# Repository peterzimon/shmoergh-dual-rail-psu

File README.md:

# +/-12V Dual rail power supply

Based on (Banana Schplit)[https://github.com/pms67/BananaSchplit] by Philip Salmony

# History

### v0.1-not-working

- well, it doesn't work. The layout is shit

### v1

- working version, using the exact same layout as Phil with Banana Schplit

#

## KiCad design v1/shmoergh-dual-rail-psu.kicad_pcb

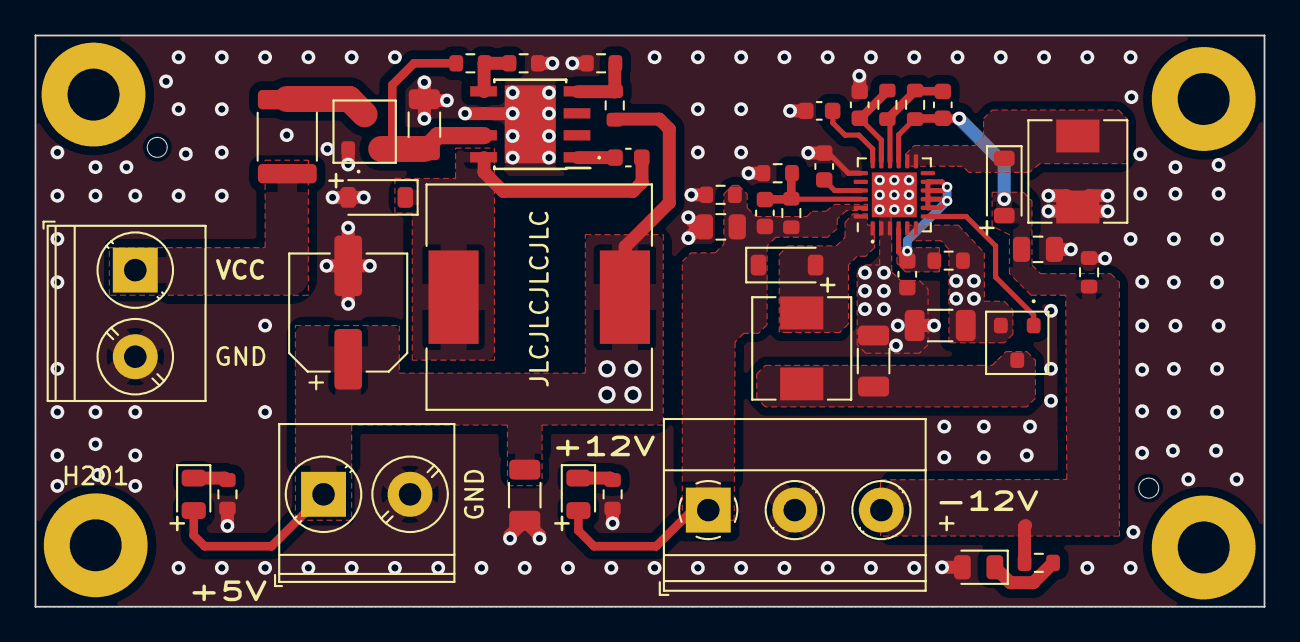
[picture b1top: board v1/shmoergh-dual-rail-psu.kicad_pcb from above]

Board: 4 copper layers, 71.0 x 33.0 mm, 49 parts (0 on the bottom side), 24 nets.

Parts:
C101, C102, C103, C107: 10u; C_1206_3216Metric
C104: 100n; C_0603_1608Metric
C105, C106: 10n; C_0603_1608Metric
C108: 6p8; C_0603_1608Metric
C109: 8p2; C_0603_1608Metric
C110: 220u; CP_Elec_6.3x7.7
C111: 220n; C_0603_1608Metric
C112, C113: 22u; C_0805_2012Metric
C114: 4n7; C_0603_1608Metric
D101, D102, D103: B5819W; D_SOD-123
D104: RED; LED_0805_2012Metric
D105: GREEN; LED_0805_2012Metric
D106: YELLOW; LED_0805_2012Metric
F101: 500mA; Fuse_1812_4532Metric
H201, H202, H203, H204: MountingHole; MountingHole_3mm_Pad
J101, J103: Screw_Terminal_01x02; TerminalBlock_Phoenix_PT-1,5-2-5.0-H_1x02_P5.00mm_Horizontal
J102: Screw_Terminal_01x03; TerminalBlock_Phoenix_MKDS-1,5-3_1x03_P5.00mm_Horizontal
L101, L103: 10u; L_Sunlord_MWSA0518S
L102: 47u; L_Sunlord_SWRB1204S
Q101, Q102: AO3401A; SOT-23
R101: 100; R_0603_1608Metric
R102, R103, R106: 100k; R_0603_1608Metric
R104, R107: 1M; R_0603_1608Metric
R105: 110k; R_0603_1608Metric
R108: 10k; R_0603_1608Metric
R109: 3k3; R_0603_1608Metric
R110, R111: 12k; R_0603_1608Metric
R112: 1k5; R_0603_1608Metric
R113: 4k3; R_0603_1608Metric
R114: 5k1; R_0603_1608Metric
U101: TPS65131RGER; QFN-24-1EP_4x4mm_P0.5mm_EP2.6x2.6mm
U102: TPS5430DDA; TI_SO-PowerPAD-8_ThermalVias

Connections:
+5V: C101.1, C107.1, C110.1, D104.2 (A), J103.1, L102.2, Q102.2 (S), R101.2, R108.2, U101.5 (INN_1), U101.6 (INN_2)
+12V: C108.1, C113.1, D101.1 (K), D105.2 (A), J102.1, R104.2, R111.2, U101.23 (VPOS)
-12V: C109.2, C112.1, D103.2 (A), J102.3, R107.1, R110.2, R114.1, U101.15 (VNEG)
GND: C101.2, C102.2, C103.2, C104.2, C106.2, C107.2, C110.2, C111.2, C112.2, C113.2, C114.2, D102.2 (A), D106.2 (A), J101.2, J102.2, J103.2, L103.2, Q101.1 (G), R103.1, R105.1, R109.1, R110.1, R111.1, R112.1, R113.1, U101.2 (PGND_1), U101.3 (PGND_2), U101.19 (AGND), U101.25 (POWERPAD), U102.6 (GND), U102.9 (GNDPAD)
unnamed: D101.2 (A), L101.2, U101.1 (INP_1), U101.24 (INP_2)
unnamed: C105.2, D102.1 (K), L102.1, U102.8 (PH)
unnamed: D103.1 (K), L103.1, U101.13 (OUTN_1), U101.14 (OUTN_2)
unnamed: D104.1 (K), R112.2
unnamed: D105.1 (K), R113.2
unnamed: D106.1 (K), R114.2
unnamed: F101.1, Q101.3 (D)
unnamed: C102.1, Q101.2 (S), R102.2, U102.7 (VIN)
unnamed: C103.1, L101.1, Q102.3 (D)
unnamed: Q102.1 (G), U101.7 (BSW)
unnamed: C114.1, U101.18 (CN)
unnamed: C106.1, U101.21 (CP)
unnamed: C104.1, R101.1, U101.4 (VIN), U101.8 (ENP), U101.9 (PSP), U101.10 (ENN), U101.11 (PSN)
unnamed: C109.1, R106.1, R107.2, U101.16 (FBN)
unnamed: C108.2, R104.1, R105.2, U101.22 (FBP)
unnamed: C111.1, R106.2, U101.17 (VREF)
unnamed: C105.1, U102.1 (BOOT)
unnamed: R102.1, R103.2, U102.5 (EN)
PSU_FB: R108.1, R109.2, U102.4 (VSENSE)
VCC: F101.2, J101.1

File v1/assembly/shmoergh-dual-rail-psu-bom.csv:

Comment,Designator,Footprint,LCSC
"10u","C101,C102,C103,C107","Capacitor_SMD:C_1206_3216Metric","C13585"
"100n","C104","Capacitor_SMD:C_0603_1608Metric","C14663"
"10n","C105,C106","Capacitor_SMD:C_0603_1608Metric","C57112"
"6p8","C108","Capacitor_SMD:C_0603_1608Metric","C1679"
"8p2","C109","Capacitor_SMD:C_0603_1608Metric","C1685"
"220u","C110","Capacitor_SMD:CP_Elec_6.3x7.7","C127327"
"220n","C111","Capacitor_SMD:C_0603_1608Metric","C21120"
"22u","C112,C113","Capacitor_SMD:C_0805_2012Metric","C45783"
"4n7","C114","Capacitor_SMD:C_0603_1608Metric","C53987"
"B5819W","D101,D102,D103","Diode_SMD:D_SOD-123","C8598"
"RED","D104","LED_SMD:LED_0805_2012Metric","C84256"
"GREEN","D105","LED_SMD:LED_0805_2012Metric","C2297"
"YELLOW","D106","LED_SMD:LED_0805_2012Metric","C2296"
"500mA","F101","Fuse:Fuse_1812_4532Metric","C151168"
"10u","L101,L103","Inductor_SMD:L_Sunlord_MWSA0518S","C181721"
"47u","L102","Inductor_SMD:L_Sunlord_SWRB1204S","C169398"
"AO3401A","Q101,Q102","PCM_Package_TO_SOT_SMD_AKL:SOT-23","C15127"
"100","R101","Resistor_SMD:R_0603_1608Metric","C22775"
"100k","R102,R103,R106","Resistor_SMD:R_0603_1608Metric","C25803"
"1M","R104,R107","Resistor_SMD:R_0603_1608Metric","C22935"
"110k","R105","Resistor_SMD:R_0603_1608Metric","C25805"
"10k","R108","Resistor_SMD:R_0603_1608Metric","C25804"
"3k3","R109","Resistor_SMD:R_0603_1608Metric","C22978"
"12k","R110,R111","Resistor_SMD:R_0603_1608Metric","C22790"
"1k5","R112","Resistor_SMD:R_0603_1608Metric","C22843"
"4k3","R113","Resistor_SMD:R_0603_1608Metric","C23159"
"5k1","R114","Resistor_SMD:R_0603_1608Metric","C23186"
"TPS65131RGER","U101","Package_DFN_QFN:QFN-24-1EP_4x4mm_P0.5mm_EP2.6x2.6mm","C87663"
"TPS5430DDA","U102","Package_SO:TI_SO-PowerPAD-8_ThermalVias","C9864"

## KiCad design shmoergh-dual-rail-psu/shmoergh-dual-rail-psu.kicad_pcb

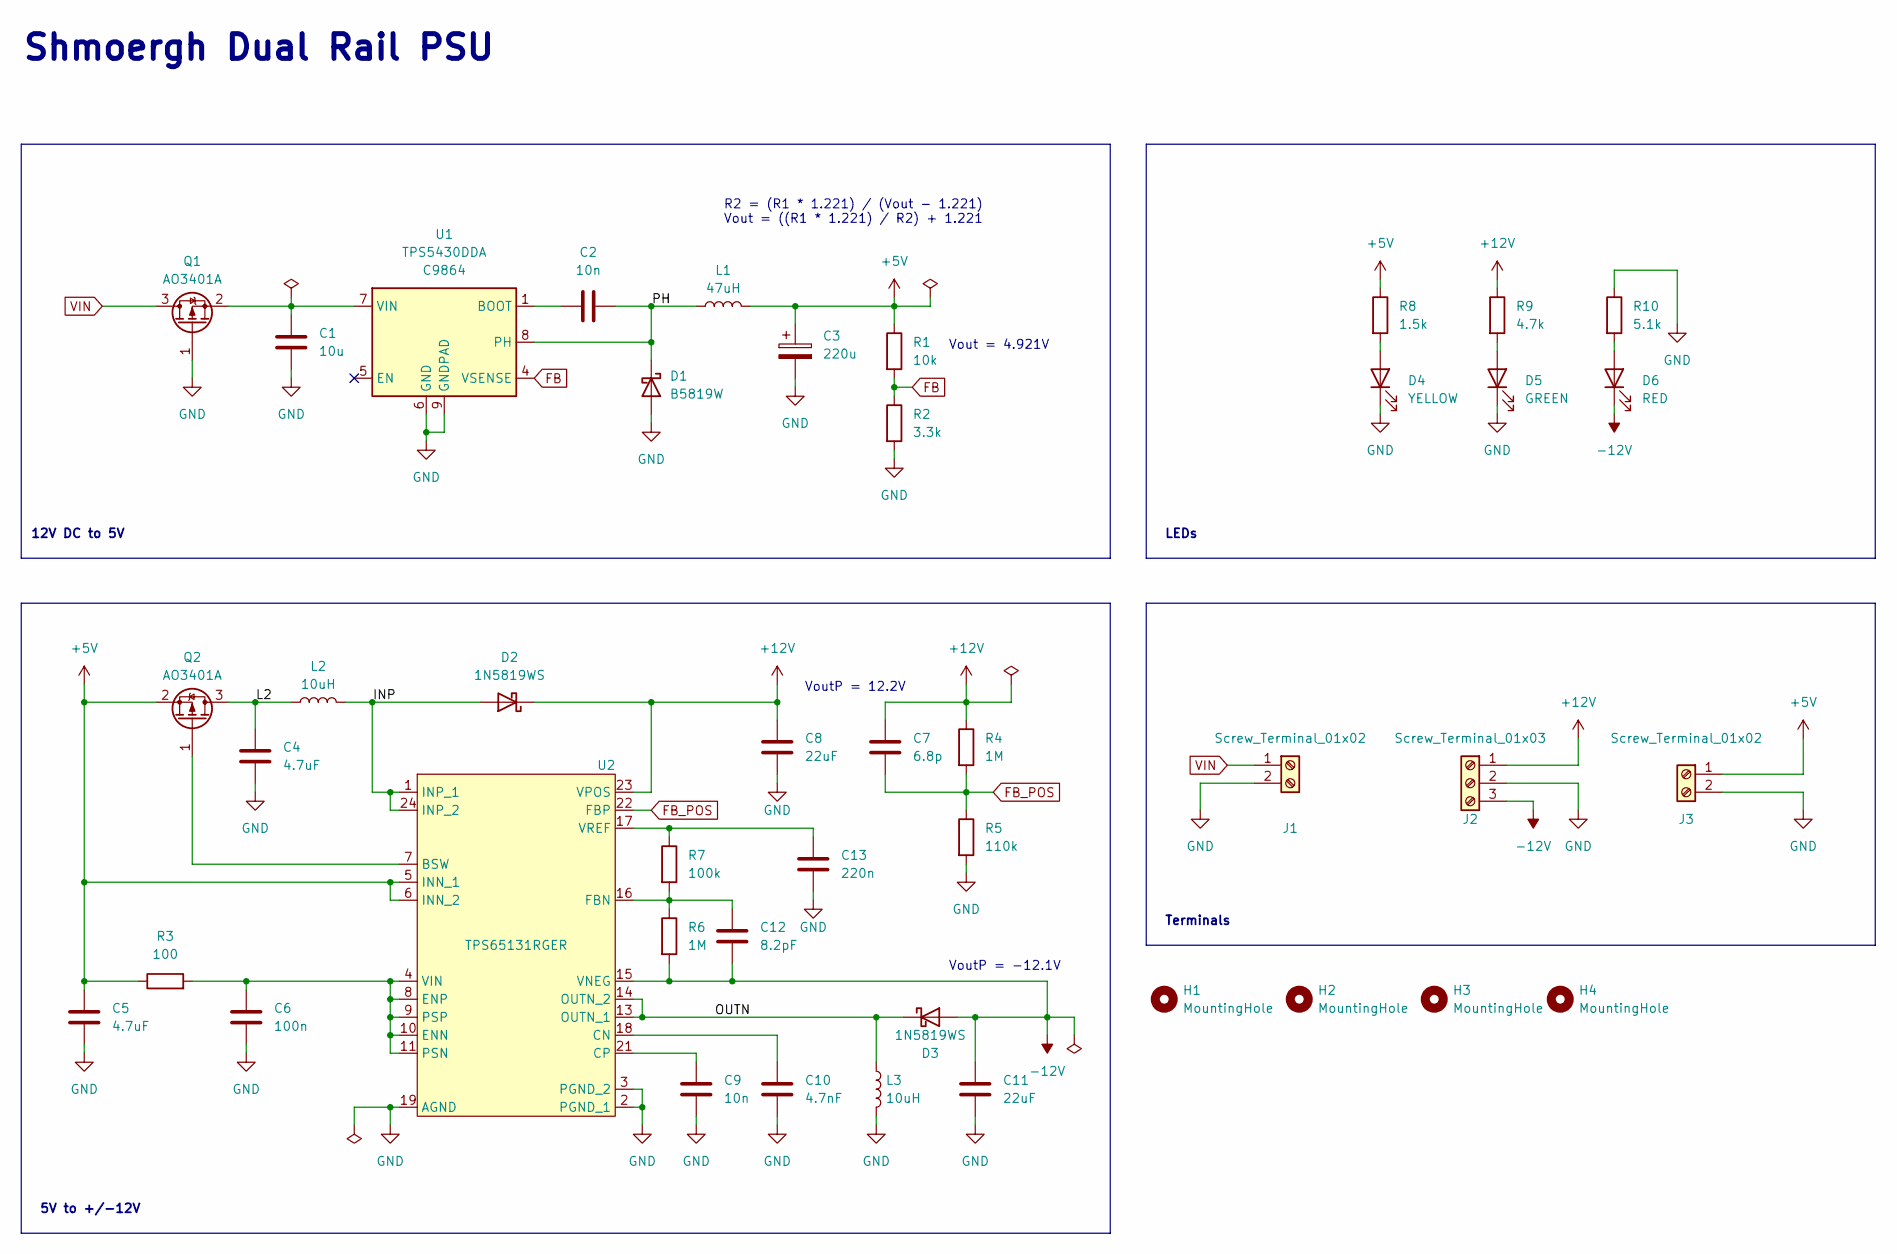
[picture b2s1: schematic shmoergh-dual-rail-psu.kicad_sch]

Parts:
C1: 10u; C_1206_3216Metric; LCSC C13585
C2: 10n; C_0402_1005Metric; LCSC C15195
C3: 220u; C_Elec_6.3x7.7; LCSC C127327
C4, C5: 4.7uF; C_0603_1608Metric; LCSC C19666
C6: 100n; C_0402_1005Metric; LCSC C307331
C7: 6.8p; R_0603_1608Metric; LCSC C1679
C8, C11: 22uF; C_0805_2012Metric; LCSC C45783
C9: 10n; C_0603_1608Metric; LCSC C57112
C10: 4.7nF; C_0603_1608Metric; LCSC C53987
C12: 8.2pF; C_0603_1608Metric; LCSC C1685
C13: 220n; C_0603_1608Metric; LCSC C21120
D1: B5819W; D_SOD-123; LCSC C8598
D2, D3: 1N5819WS; D_SOD-123; LCSC C191023
D4: YELLOW; LED_0603_1608Metric; LCSC C72038
D5: GREEN; LED_0603_1608Metric; LCSC C72043
D6: RED; LED_0603_1608Metric; LCSC C2286
H1, H2, H3, H4: MountingHole; MountingHole_3mm_Pad_Via
J1, J3: Screw_Terminal_01x02; TerminalBlock_Phoenix_MKDS-1,5-2_1x02_P5.00mm_Horizontal
J2: Screw_Terminal_01x03; TerminalBlock_Phoenix_MKDS-1,5-3_1x03_P5.00mm_Horizontal
L1: 47uH; L_Sunlord_SWRB1204S; LCSC C169398
L2, L3: 10uH; L_Sunlord_MWSA0518S; LCSC C177248
Q1, Q2: AO3401A; SOT-23; LCSC C15127
R1: 10k; R_0603_1608Metric; LCSC C25804
R2: 3.3k; R_0603_1608Metric; LCSC C22978
R3: 100; R_0603_1608Metric; LCSC C22775
R4, R6: 1M; R_0603_1608Metric; LCSC C22935
R5: 110k; R_0603_1608Metric; LCSC C25805
R7: 100k; R_0603_1608Metric; LCSC C25803
R8: 1.5k; R_0402_1005Metric; LCSC C25867
R9: 4.7k; R_0402_1005Metric; LCSC C25900
R10: 5.1k; R_0402_1005Metric; LCSC C25905
U1: TPS5430DDA; TI_SO-PowerPAD-8_ThermalVias; LCSC C9864
U2: TPS65131RGER; QFN-24-1EP_4x4mm_P0.5mm_EP2.6x2.6mm; LCSC TPS65131RGER

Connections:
+5V: C3.1, C5.1, J3.1, L1.2, Q2.2 (S), R1.1, R3.1, R8.1, U2.5 (INN_1), U2.6 (INN_2)
+12V: C7.1, C8.1, D2.1 (K), J2.1, R4.1, R9.1, U2.23 (VPOS)
-12V: C11.1, C12.2, D3.2 (A), D6.1 (K), J2.3, R6.2, U2.15 (VNEG)
/INP: D2.2 (A), L2.2, U2.1 (INP_1), U2.24 (INP_2)
/L2: C4.1, L2.1, Q2.3 (D)
/OUTN: D3.1 (K), L3.1, U2.13 (OUTN_1), U2.14 (OUTN_2)
/PH: C2.2, D1.1 (K), L1.1, U1.8 (PH)
FB: R1.2, R2.1, U1.4 (VSENSE)
FB_POS: C7.2, R4.2, R5.1, U2.22 (FBP)
GND: C1.2, C3.2, C4.2, C5.2, C6.2, C8.2, C9.2, C10.2, C11.2, C13.2, D1.2 (A), D4.1 (K), D5.1 (K), J1.2, J2.2, J3.2, L3.2, Q1.1 (G), R2.2, R5.2, R10.1, U1.6 (GND), U1.9 (GNDPAD), U2.2 (PGND_1), U2.3 (PGND_2), U2.19 (AGND), U2.25
unnamed: D4.2 (A), R8.2
unnamed: D5.2 (A), R9.2
unnamed: D6.2 (A), R10.2
unnamed: C1.1, Q1.2 (S), U1.7 (VIN)
unnamed: Q2.1 (G), U2.7 (BSW)
unnamed: C2.1, U1.1 (BOOT)
unnamed: C10.1, U2.18 (CN)
unnamed: C9.1, U2.21 (CP)
unnamed: C6.1, R3.2, U2.4 (VIN), U2.8 (ENP), U2.9 (PSP), U2.10 (ENN), U2.11 (PSN)
unnamed: C12.1, R6.1, R7.2, U2.16 (FBN)
unnamed: C13.1, R7.1, U2.17 (VREF)
VIN: J1.1, Q1.3 (D)

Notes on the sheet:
R2 = (R1 * 1.221) / (Vout - 1.221) Vout = ((R1 * 1.221) / R2) + 1.221
Terminals
VoutP = -12.1V
LEDs
Vout = 4.921V
VoutP = 12.2V
12V DC to 5V
5V to +/-12V
Shmoergh Dual Rail PSU

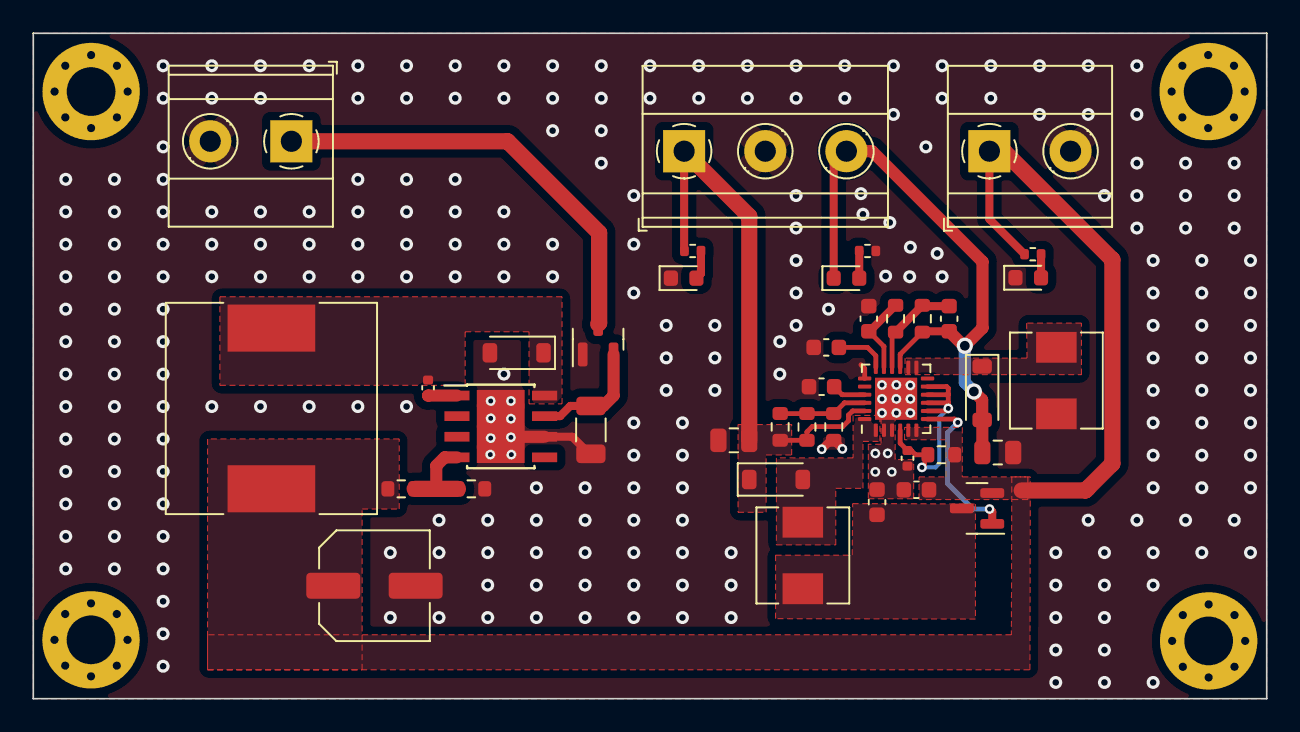
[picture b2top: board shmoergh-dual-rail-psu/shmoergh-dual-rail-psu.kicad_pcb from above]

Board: 2 copper layers, 76.0 x 41.0 mm, 43 parts (0 on the bottom side), 22 nets.

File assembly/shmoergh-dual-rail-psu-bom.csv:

Comment,Designator,Footprint,LCSC
"10u","C1","Capacitor_SMD:C_1206_3216Metric","C13585"
"4.7nF","C10","Capacitor_SMD:C_0603_1608Metric","C53987"
"8.2pF","C12","Capacitor_SMD:C_0603_1608Metric","C1685"
"220n","C13","Capacitor_SMD:C_0603_1608Metric","C21120"
"10n","C2","Capacitor_SMD:C_0402_1005Metric","C15195"
"220u","C3","Capacitor_SMD:C_Elec_6.3x7.7","C127327"
"4.7uF","C4,C5","Capacitor_SMD:C_0603_1608Metric","C19666"
"100n","C6","Capacitor_SMD:C_0402_1005Metric","C307331"
"6.8p","C7","Resistor_SMD:R_0603_1608Metric","C1679"
"22uF","C8,C11","Capacitor_SMD:C_0805_2012Metric","C45783"
"10n","C9","Capacitor_SMD:C_0603_1608Metric","C57112"
"B5819W","D1","Diode_SMD:D_SOD-123","C8598"
"1N5819WS","D2,D3","Diode_SMD:D_SOD-123","C191023"
"YELLOW","D4","LED_SMD:LED_0603_1608Metric","C72038"
"GREEN","D5","LED_SMD:LED_0603_1608Metric","C72043"
"RED","D6","LED_SMD:LED_0603_1608Metric","C2286"
"47uH","L1","Inductor_SMD:L_Sunlord_SWRB1204S","C169398"
"10uH","L2,L3","Inductor_SMD:L_Sunlord_MWSA0518S","C177248"
"AO3401A","Q1,Q2","Package_TO_SOT_SMD:SOT-23","C15127"
"10k","R1","Resistor_SMD:R_0603_1608Metric","C25804"
"5.1k","R10","Resistor_SMD:R_0402_1005Metric","C25905"
"3.3k","R2","Resistor_SMD:R_0603_1608Metric","C22978"
"100","R3","Resistor_SMD:R_0603_1608Metric","C22775"
"1M","R4,R6","Resistor_SMD:R_0603_1608Metric","C22935"
"110k","R5","Resistor_SMD:R_0603_1608Metric","C25805"
"100k","R7","Resistor_SMD:R_0603_1608Metric","C25803"
"1.5k","R8","Resistor_SMD:R_0402_1005Metric","C25867"
"4.7k","R9","Resistor_SMD:R_0402_1005Metric","C25900"
"TPS5430DDA","U1","Package_SO:TI_SO-PowerPAD-8_ThermalVias","C9864"
"TPS65131RGER","U2","Package_DFN_QFN:QFN-24-1EP_4x4mm_P0.5mm_EP2.6x2.6mm","C87663"

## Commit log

2023-09-28 Readme
2023-09-28 Added schematics and PCB
2023-09-28 Added gitignore
2023-10-03 Component update
2023-11-18 Added working version v1
2023-11-18 Cleanup lock file
